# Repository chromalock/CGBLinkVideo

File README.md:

# CGBLinkVideo

Playing media on a gameboy color over the link cable, with the help of an [RPi Pico](https://www.raspberrypi.com/products/raspberry-pi-pico/)

# Inspiration

This project was heavily inspired by [Staacks/wifi-game-boy-cartridge](https://github.com/Staacks/wifi-game-boy-cartridge), and
borrows utility macros, cartridge headers, and some random python snippets.

# Repo Structure

You can find more detailed information on the individual components in the following locations:

```
/firmware/  |   Firmware + PIO programs for an RPi Pico (W)
/pcb/       |   Schematics, PCB designs, and gerber files for the GBLink board.
/roms/      |   Gameboy Color ROMs
/scripts/   |   Python package + scripts for streaming data to the gameboy color 
/stream/    |   Wrapper scripts for hooking up video sources to the gameboy script
```

# System Requirements
```
- Python 3  (3.10.12 for me)
- FFMpeg    (4.4.2-0ubuntu0.22.04.1 for me)
- RGBASM    (v0.7.0-37-gc70cecc2 for me)        <-- only if you want to build the roms yourself
```

# Hardware Requirements
```
- Gameboy Color + Link Cable
- Raspberry PI Pico
- GBLink Board (or some other method of level shifting)
- GBC Flash Cartridge
```

# Conceptual Overview

```
| PC | <--UART--> | RPi Pico + GBLink Board | <--PIO--> | Gameboy Color | 
```

PC Handles video encoding, then sends the encoded data to the RPi pico over UART, which is stored in a buffer (triple buffered). 
This happens at roughly 1Mbps.

Meanwhile, the Gameboy color makes requests to the RPi Pico over its serial port, with the voltage levels being shifted by the GBLink board.
The PIO handle the job of parsing these signals and shifting data out to the gameboy.

# Explanation Video

# Quickstart

First, you will need to put the files from [this release](https://github.com/chromalock/CGBLinkVideo/releases/tag/1.0) onto a gameboy flash cartridge. (or you can choose only the rom files you need)

Plug in your GBLink adapter to your computer and connect it to your gameboy. On the gameboy, start the rom file you need for your application. (view the above release for the descriptions)

## OBS

You will need [OBS](https://obsproject.com/).

## Linux

```bash
# install dependencies
git clone https://github.com/chromalock/CGBLinkVideo
cd CGBLinkVideo

sudo apt install ffmpeg 
pip install -r ./scripts/requirements.txt
```

get list of video devices (optional)
```bash
# get list of current video devices
v4l2-ctl --list-devices
# Dummy video device (0x0000) (platform:v4l2loopback-000):
#         /dev/video0
```

get list of serial ports
```bash
sudo dmesg | grep tty
# [484956.666636] cdc_acm 3-4.1.2.1.4:1.0: ttyACM0: USB ACM device
```

run appropriate script
```bash
# td2018.gbc            | bw stream
# td2018-vsync.gbc      | bw stream, but with larger transfers to reduce tearing
./stream/cam-stream-full.sh /dev/video0 /dev/ttyACM0

# tdc2018.gbc           | color stream
# tdc2018-vsync.gbc     | color stream, but with larger transfers to reduce tearing
./stream/color-cam-stream-full.sh /dev/video0 /dev/ttyACM0

# tile-index.gbc        |  the low-res grayscale stream that sends a new tilemap every frame
./stream/cam-stream.sh /dev/video0 /dev/ttyACM0
```

## Windows

You will need to install ffmpeg from [here](https://www.ffmpeg.org/download.html), and Python 3 from [here](https://www.python.org/)

I recommend using [`choco`](https://chocolatey.org/) to do it via `choco install ffmpeg-full` and `choco install python`.

To get `pip`, run:
```batch
python -m pip install -U pip
```

then, clone the repository (or you can download/extract the [zip file](https://github.com/chromalock/CGBLinkVideo/archive/refs/heads/main.zip))

```batch
git clone https://github.com/chromalock/CGBLinkVideo
cd CGBLinkVideo
```

install python dependencies:
```batch
pip install -r .\scripts\requirements.txt
```

Get list of serial ports
```batch
mode
:: Status for device COM3:
:: -----------------------
::     Baud:            115200
::     Parity:          None
::     Data Bits:       8
::     Stop Bits:       1
::     Timeout:         OFF
::     XON/XOFF:        OFF
::     CTS handshaking: OFF
::     DSR handshaking: OFF
::     DSR sensitivity: OFF
::     DTR circuit:     OFF
::     RTS circuit:     ON
:: 
:: 
:: Status for device CON:
:: ----------------------
::     Lines:          3000
::     Columns:        120
::     Keyboard rate:  31
::     Keyboard delay: 1
::     Code page:      437
```

then (in cmd.exe, powershell will not work) run the script for whichever rom you are running 
```batch
:: td2018.gbc            | bw stream
:: td2018-vsync.gbc      | bw stream, but with larger transfers to reduce tearing
.\stream\cam-stream-full.sh COM3

:: tdc2018.gbc           | color stream
:: tdc2018-vsync.gbc     | color stream, but with larger transfers to reduce tearing
.\stream\color-cam-stream-full.bat COM3

:: tile-index.gbc        |  the low-res grayscale stream that sends a new tilemap every frame
.\stream\cam-stream.bat COM3
```

# Known Issues

## Not responding after stopping stream

Due to either my bad code or an issue in the `pySerialTransfer` library, occasionally when stopping the stream program the arduino will be left in a state where it wont respond any more.

The solution is to simply unplug and re-plug in the GBLink. After this, the serial port name may change and you will need to determine which is the new one via the steps above.

## Seeing garbage data or just Black

### 1. Pico not synced to GB
Hold right on the dpad of the gameboy for a few seconds. This should allow enough time for the pico to reset its state machines, and will restart communication on the gameboy.

### 2. Bad Connection
If the link cable isnt making good contact with either tha gameboy or the gblink, data may not transfer. Try a different link cable or cleaning the contacts on both devices.

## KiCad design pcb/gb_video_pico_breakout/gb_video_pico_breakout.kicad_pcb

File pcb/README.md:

# pcb

# Principle Of Operation

3.3V is supplied to the board via the RPi pico, and 5V supplied from the Gameboy Color's link port.\*

Capacitors `C1, C2` are decoupling capacitors.

Diodes `D1, D2` are status LEDs for the 3.3V and 5V power rails, current-limited by `Rx, Ry`.

ICs `U1, U2, U3` are noninverting schmitt-trigger buffers [SN74LVC1G17-Q1](https://www.ti.com/lit/ds/symlink/sn74lvc1g17-q1.pdf?ts=1731651431162).
They increase signal quality and convert between 3.3V and 5V signals on the TX, RX, and Clock lines.

\**Using 5V from the pico results in dropped bits for reasons I am unqualified to answer. Seems to be related to backfeeding into the gameboy.*

# Circuit Diagram

# Limitations

Due to using a unidirectional level shifter on the clock line, the RPi Pico is unable to act as a controller, relying on the gameboy to initiate transactions.
Attempting to use the RPi Pico as a controller could result in shorting the output of the clock level shifter to ground. It would be unlikely that this would damage
the gameboy, but would potentially damage both the GBLink board and the RPi Pico.

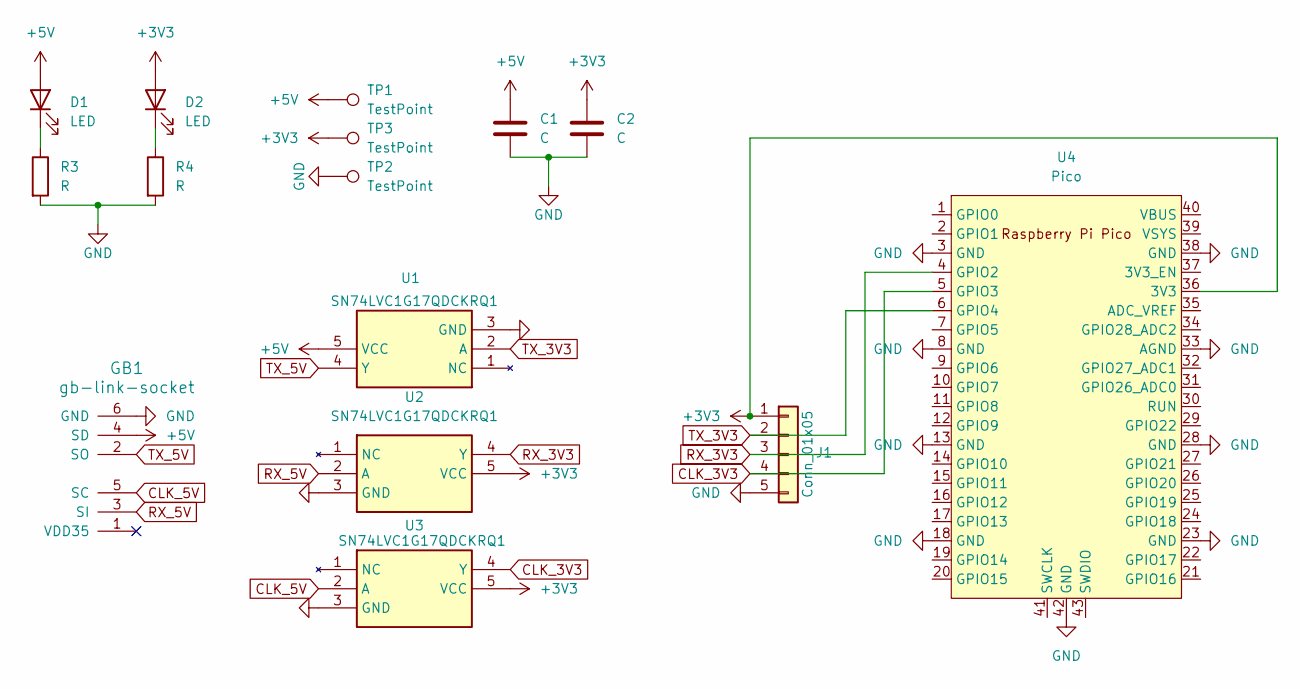
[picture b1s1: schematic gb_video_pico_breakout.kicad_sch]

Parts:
C1, C2: C; C_0805_2012Metric
D1, D2: LED; LED_0805_2012Metric; Mouser Part Number 630-HSMS-C177
GB1: gb-link-socket
J1: Conn_01x05; PinHeader_1x05_P2.54mm_Vertical
R3, R4: R; R_0805_2012Metric
TP1, TP2, TP3: TestPoint; PinHeader_1x01_P2.54mm_Vertical
U1, U2, U3: SN74LVC1G17QDCKRQ1; SOT65P210X110-5N; Manufacturer_Part_Number SN74LVC1G17QDCKRQ1
U4: Pico; RPi_Pico_SMD_TH

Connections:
+3V3: C2.1, D2.2 (A), J1.1, TP3.1, U2.5 (VCC), U3.5 (VCC), U4.36 (3V3)
+5V: C1.1, D1.2 (A), GB1.4 (SD), TP1.1, U1.5 (VCC)
CLK_3V3: J1.4, U3.4 (Y), U4.5 (GPIO3)
CLK_5V: GB1.5 (SC), U3.2 (A)
GND: C1.2, C2.2, GB1.6 (GND), J1.5, R3.2, R4.2, TP2.1, U1.3 (GND), U2.3 (GND), U3.3 (GND), U4.3 (GND), U4.8 (GND), U4.13 (GND), U4.18 (GND), U4.23 (GND), U4.28 (GND), U4.33 (AGND), U4.38 (GND), U4.42 (GND)
unnamed: D1.1 (K), R3.1
unnamed: D2.1 (K), R4.1
RX_3V3: J1.3, U2.4 (Y), U4.4 (GPIO2)
RX_5V: GB1.3 (SI), U2.2 (A)
TX_3V3: J1.2, U1.2 (A), U4.6 (GPIO4)
TX_5V: GB1.2 (SO), U1.4 (Y)

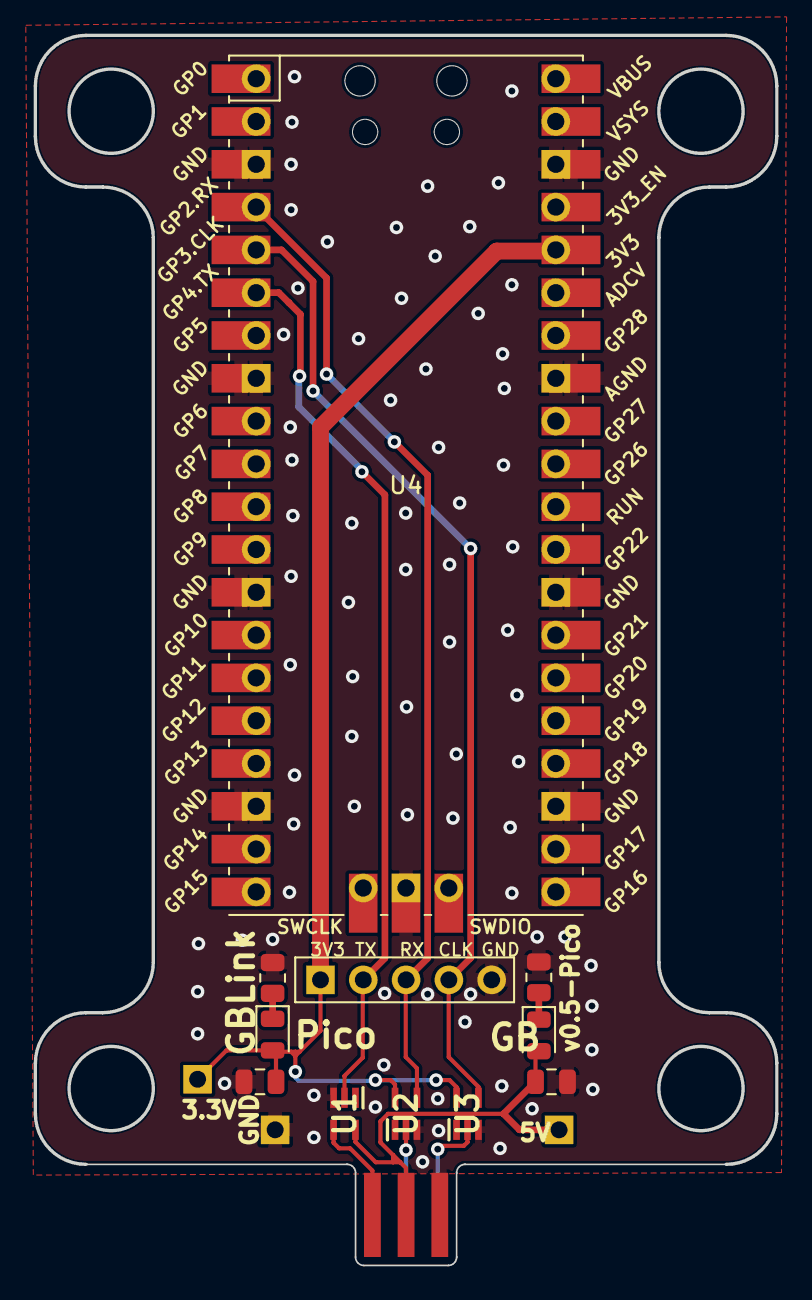
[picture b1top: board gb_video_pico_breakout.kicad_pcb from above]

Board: 11 copper layers, 44.0 x 73.0 mm, 15 parts (0 on the bottom side), 11 nets.

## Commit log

2024-11-16 remove unused
2024-11-16 change title
2024-11-16 V0.5
2024-11-16 remove
2024-11-16 restructure
2024-11-16 rearrange
2024-11-16 add main makefile
2024-11-17 fix timing issues?
2024-11-17 buffers
2024-11-17 I dont know why this works
2024-11-17 fixed it but i have no clue how
2024-11-17 more encoding?
2024-11-17 work on rotations
2024-11-17 add DMA
2024-11-17 spewwing
2024-11-18 whoops name
2024-11-18 update structure again
2024-11-18 name
2024-11-18 formatting
2024-11-18 update versions
2024-11-18 versions
2024-11-18 update files
2024-11-18 clean up macros
2024-11-19 real dumbass hours (dec bc)
2024-11-19 full stream
2024-11-19 better defaults
2024-11-19 full screen streaming
2024-11-22 Generic buffer
2024-11-24 add serialtransfer support
2024-11-25 re-introduce old stuff
2024-11-25 add coffee link
2024-11-28 updates for streaming
2024-11-28 streams
2024-12-06 fixed
2024-12-12 add color
2024-12-20 update for gh
2024-12-20 remove midi
2024-12-21 update structure
2025-01-05 window script test
2025-01-05 windows support
